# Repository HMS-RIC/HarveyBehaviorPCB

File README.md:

# HarveyBehaviorPCB v2
Circuit board for Harvey Lab VR behavior rigs

## Features
This board is designed to integrate a Teensy microcontroller and a National Instruments DAQ board (NI USB-600x) with the sensors and actuators on the behavior rig. Importantly, the board is used to convey the spherical treadmill movement signals to the VR computer. The Teensy makes a digital connection to the two ball movement sensors (mounted on the base of the spherical treadmill) to make continuous reading of ball movement. It then produces three analog outputs, representing velocity in the _Yaw_, _Pitch_, and _Roll_ axes, that are read into the VR computer by the DAQ board.

Other optional features of the PCB are: 
- Driver circuit for 2 solenoid valves (e.g. for liquid rewards)
- Two lick detector circuits
- A photodiode amplifier
- Many expansion ports/connectors: BNC connections, 0.1" headers, and a serial I2C connection (Qwiic connector)

## Fabrication
The full fabrication design is included in the [Gerber Zip File](PCB_v2_KiCAD/Gerbers/HarveyBehaviorPCB_v2.zip?raw=true). You can upload this file to any PCB fabricator to get a quote and place an order. (The board does not have any special features, so the default settings for PCB manufacture are probably fine.) One a relatively low-cost option for a board this size is the $33/board (3 board minimum) special at [Advanced Circuits](https://www.advancedpcb.com/en-us/33-each-special/).

## Assembly
The [Bill of Materials](HarveyBehaviorPCB_v2_BOM.xlsx?raw=true) (BOM) file has the full list of components. Everything but the optional I2C connector is a through-hole part and can be soldered on with a simple soldering iron (and [proper technique](https://mightyohm.com/files/soldercomic/FullSolderComic_EN.pdf)). The board is divided up into labeled regions that describe their high-level function and allow you to populate only the subset of components that you plan to use:
- **Ball sensor connectors**: The board is designed to work with two types of ball sensor ([ADNS-9800](https://www.tindie.com/products/citizenjoe/adns-9800-motion-sensor/) and [PMW3360](https://www.tindie.com/products/citizenjoe/pmw3360-motion-sensor/)). Chose one and populate the appropriate connector. (Also be sure to use the correct Teensy firmware for your ball sensor.)
- **Valve driver circuit**, **Lick and photodiode circuits**: These are optional functionalities. Only populate these regions if you plan to use them.
- **LP filters for velocity signals**: These are not optional. They low-pass filter the Teensy's digital (PWM) output to form a smooth analog signal for the NI board to acquire.
- **User 3/4 voltage-limiting circuit**: This is necessary if you plan to use the NI board's analog output pins (_AO-0_, _AO-1_) to control the voltage on _User-3_ and _User-4_. This circuit protects the Teensy from an accidental +5V output from the NI board (since the Teensy 4.0 cannot handle >3.3V inputs).
- **Jumpers JP2, JP3**: Optional. Short these jumpers (i.e., connect the pins within each jumper) to enable the NI analog output (_AO-0/1_, a.k.a. _User-3/4_) to control the valves.
- **Jumpers JP4, JP5**: Optional. In their default state they enable the I2C connector and disable the _MOT1_/_MOT2_ connections to the ball sensors. The _MOTx_ lines are not used during typical operation, so these jumpers are unlikely to be used.

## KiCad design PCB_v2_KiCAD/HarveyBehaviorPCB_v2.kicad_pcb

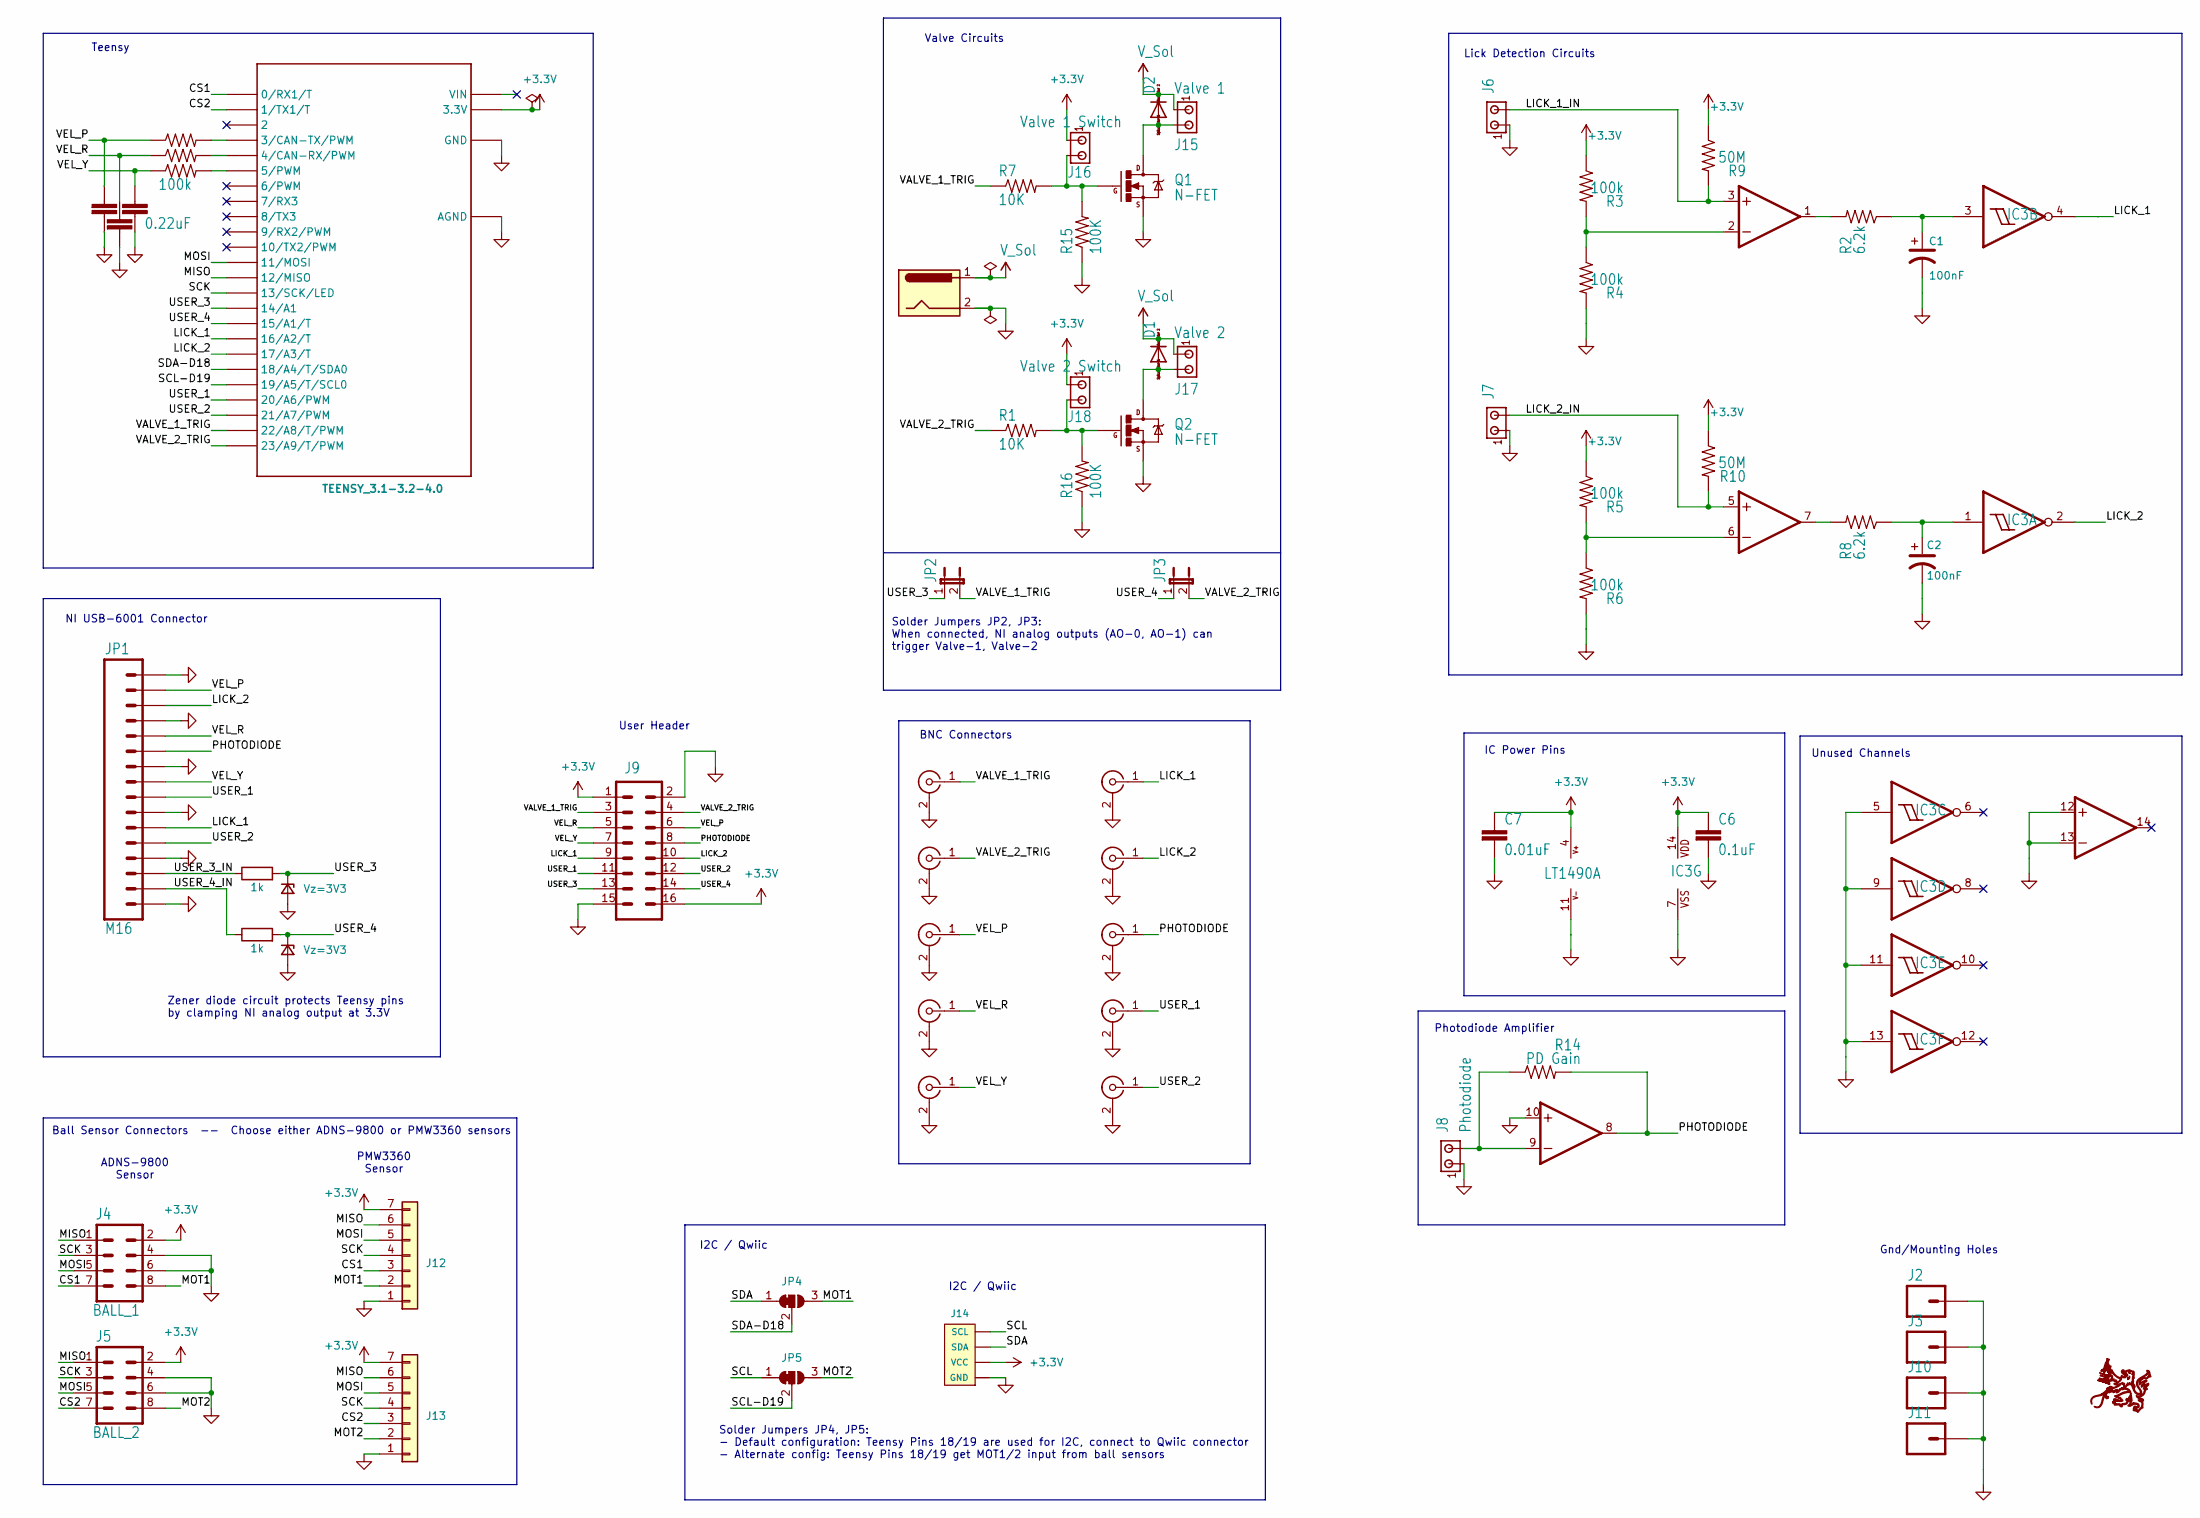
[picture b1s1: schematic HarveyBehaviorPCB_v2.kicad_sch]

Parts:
C1, C2: 100nF; CPOL-RADIAL-10UF-25V
C3, C4, C5: 0.22uF; CAP-PTH-SMALL2
C6: 0.1uF; CAP-PTH-SMALL-KIT
C7: 0.01uF; CAP-PTH-SMALL-KIT
D1, D2: 1N4148; DO41-10
D3, D4: Vz=3V3; D_DO-34_SOD68_P7.62mm_Horizontal
IC1: LT1490A; DIP-14_W7.62mm_LongPads
IC3: 40106N; DIP-14_W7.62mm_LongPads
J1: POWER_JACKPTH; POWER_JACK_PTH
J2, J3, J10, J11: M01SMTSO-256-ET-0.165DIA; SMTSO-256-ET-0.165DIA
J4: BALL_1; 2X4
J5: BALL_2; 2X4
J6, J7: MTA02-100; 10X02MTA
J8: Photodiode; 10X02MTA
J9: M08X2; 2X8
J12, J13: Conn_01x07; CON_535170730_MOL
J14: I2C_STANDARDQWIIC; 1X04_1MM_RA
J15: Valve 1; 10X02MTA
J16: Valve 1 Switch; 10X02MTA
J17: Valve 2; 10X02MTA
J18: Valve 2 Switch; 10X02MTA
JP1: M16; 1X16_TERM_BLOCK_0.15_
JP2, JP3: JUMPER-2PTH; 1X02
JP4, JP5: SolderJumper_3_Bridged12; SolderJumper-3_P1.3mm_Bridged12_RoundedPad1.0x1.5mm
Q1, Q2: N-FET; TO220V
R1, R7: 10K; AXIAL-0.5
R2, R8: 6.2k; AXIAL-0.5
R3, R4, R5, R6, R11, R12, R13: 100k; AXIAL-0.5
R9, R10: 50M; AXIAL-0.5
R14: PD Gain; AXIAL-0.5
R15, R16: 100K; AXIAL-0.5
R17, R18: 1k; R_Axial_DIN0207_L6.3mm_D2.5mm_P10.16mm_Horizontal
TEENSY0: TEENSY_3.1-3.2-4.0; TEENSY_3.0-3.2&LC_DIL
U$1, U$2, U$3, U$4, U$5, U$6, U$7, U$8, U$9, U$10: BNCPTH; BNC_Amphenol_B6252HB-NPP3G-50_Horizontal

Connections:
+3.3V: C6.1, C7.1, IC1.4 (V+), IC3.14 (VDD), J4.2, J5.2, J9.1, J9.16, J12.7, J13.7, J14.2 (VCC), J16.1, J18.1, R3.P$1 (1), R5.P$1 (1), R9.P$1 (1), R10.P$1 (1), TEENSY0.3.3V
/CS1: J4.7, J12.3, TEENSY0.0 (0/RX1/T)
/CS2: J5.7, J13.3, TEENSY0.1 (1/TX1/T)
/LICK_1: IC3.4 (O), J9.9, JP1.6, JP1.22 (6), TEENSY0.16/A2 (16/A2/T), U$6.1 (In)
/LICK_1_IN: IC1.3 (+IN), J6.2, R9.P$2 (2)
/LICK_2: IC3.2 (O), J9.10, JP1.14, JP1.30 (14), TEENSY0.17/A3 (17/A3/T), U$7.1 (In)
/LICK_2_IN: IC1.5 (+IN), J7.2, R10.P$2 (2)
/MISO: J4.1, J5.1, J12.6, J13.6, TEENSY0.12 (12/MISO)
/MOSI: J4.5, J5.5, J12.5, J13.5, TEENSY0.11 (11/MOSI)
/MOT1: J4.8, J12.2, JP4.3 (B)
/MOT2: J5.8, J13.2, JP5.3 (B)
/PHOTODIODE: IC1.8 (OUT), J9.8, JP1.11, JP1.27 (11), R14.P$2 (2), U$8.1 (In)
/SCK: J4.3, J5.3, J12.4, J13.4, TEENSY0.13 (13/SCK/LED)
/SCL: J14.4 (SCL), JP5.1 (A)
/SCL-D19: JP5.2 (C), TEENSY0.19/A5 (19/A5/T/SCL0)
/SDA: J14.3 (SDA), JP4.1 (A)
/SDA-D18: JP4.2 (C), TEENSY0.18/A4 (18/A4/T/SDA0)
/USER_1: J9.11, JP1.8, JP1.24 (8), TEENSY0.20/A6 (20/A6/PWM), U$9.1 (In)
/USER_2: J9.12, JP1.5, JP1.21 (5), TEENSY0.21/A7 (21/A7/PWM), U$10.1 (In)
/USER_3: D4.1 (K), J9.13, JP2.1, R18.2, TEENSY0.14/A0 (14/A1)
/USER_3_IN: JP1.3, JP1.19 (3), R18.1
/USER_4: D3.1 (K), J9.14, JP3.1, R17.2, TEENSY0.15/A1 (15/A1/T)
/USER_4_IN: JP1.2, JP1.18 (2), R17.1
/VALVE_1_TRIG: J9.3, JP2.2, R7.P$1 (1), TEENSY0.22/A8 (22/A8/T/PWM), U$1.1 (In)
/VALVE_2_TRIG: J9.4, JP3.2, R1.P$1 (1), TEENSY0.23/A9 (23/A9/T/PWM), U$2.1 (In)
/VEL_P: C5.1, J9.6, JP1.15, JP1.31 (15), R13.P$1 (1), U$3.1 (In)
/VEL_R: C4.1, J9.5, JP1.12, JP1.28 (12), R12.P$1 (1), U$4.1 (In)
/VEL_Y: C3.1, J9.7, JP1.9, JP1.25 (9), R11.P$1 (1), U$5.1 (In)
GND: C1.2 (-), C2.2, C3.2, C4.2, C5.2, C6.2, C7.2, D3.2 (A), D4.2 (A), IC1.10 (+IN), IC1.11 (V-), IC1.12 (+IN), IC1.13 (-IN), IC3.5 (I), IC3.7 (VSS), IC3.9 (I), IC3.11 (I), IC3.13 (I), J1.2, J2.P$1 (1), J3.P$1 (1), J4.4, J4.6, J5.4, J5.6, J6.1, J7.1, J8.1, J9.2, J9.15, J10.P$1 (1), J11.P$1 (1), J12.1, J13.1, J14.1 (GND), JP1.1, JP1.4, JP1.7, JP1.10, JP1.13, JP1.16, JP1.17 (1), JP1.20 (4), JP1.23 (7), JP1.26 (10), JP1.29 (13), JP1.32 (16), Q1.3 (S), Q2.3 (S), R4.P$2 (2), R6.P$2 (2), R15.P$1 (1), R16.P$1 (1), TEENSY0.AGND, TEENSY0.GND, U$1.2 (Ext), U$2.2 (Ext), U$3.2 (Ext), U$4.2 (Ext), U$5.2 (Ext), U$6.2 (Ext), U$7.2 (Ext), U$8.2 (Ext), U$9.2 (Ext), U$10.2 (Ext)
unnamed: C1.1 (+), IC3.3 (I), R2.P$1 (1)
unnamed: IC1.2 (-IN), R3.P$2 (2), R4.P$1 (1)
unnamed: IC1.1 (OUT), R2.P$2 (2)
unnamed: IC1.6 (-IN), R5.P$2 (2), R6.P$1 (1)
unnamed: IC1.7 (OUT), R8.P$2 (2)
unnamed: IC1.9 (-IN), J8.2, R14.P$1 (1)
unnamed: C2.1, IC3.1 (I), R8.P$1 (1)
unnamed: D2.A, J15.2, Q1.2 (D)
unnamed: J16.2, Q1.1 (G), R7.P$2 (2), R15.P$2 (2)
unnamed: D1.A, J17.2, Q2.2 (D)
unnamed: J18.2, Q2.1 (G), R1.P$2 (2), R16.P$2 (2)
unnamed: R11.P$2 (2), TEENSY0.5 (5/PWM)
unnamed: R12.P$2 (2), TEENSY0.4 (4/CAN-RX/PWM)
unnamed: R13.P$2 (2), TEENSY0.3 (3/CAN-TX/PWM)
V_Sol: D1.C, D2.C, J1.1, J15.1, J17.1

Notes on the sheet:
NI USB-6001 Connector
Zener diode circuit protects Teensy pins by clamping NI analog output at 3.3V
BNC Connectors
Lick Detection Circuits
I2C / Qwiic
Photodiode Amplifier
Valve Circuits
Gnd/Mounting Holes
User Header
ADNS-9800 Sensor
Solder Jumpers JP4, JP5: - Default configuration: Teensy Pins 18/19 are used for I2C, connect to Qwiic connector - Alternate config: Teensy Pins 18/19 get MOT1/2 input from ball sensors
IC Power Pins
Teensy
Solder Jumpers JP2, JP3: When connected, NI analog outputs (AO-0, AO-1) can trigger Valve-1, Valve-2
Unused Channels
PMW3360 Sensor
Ball Sensor Connectors -- Choose either ADNS-9800 or PMW3360 sensors

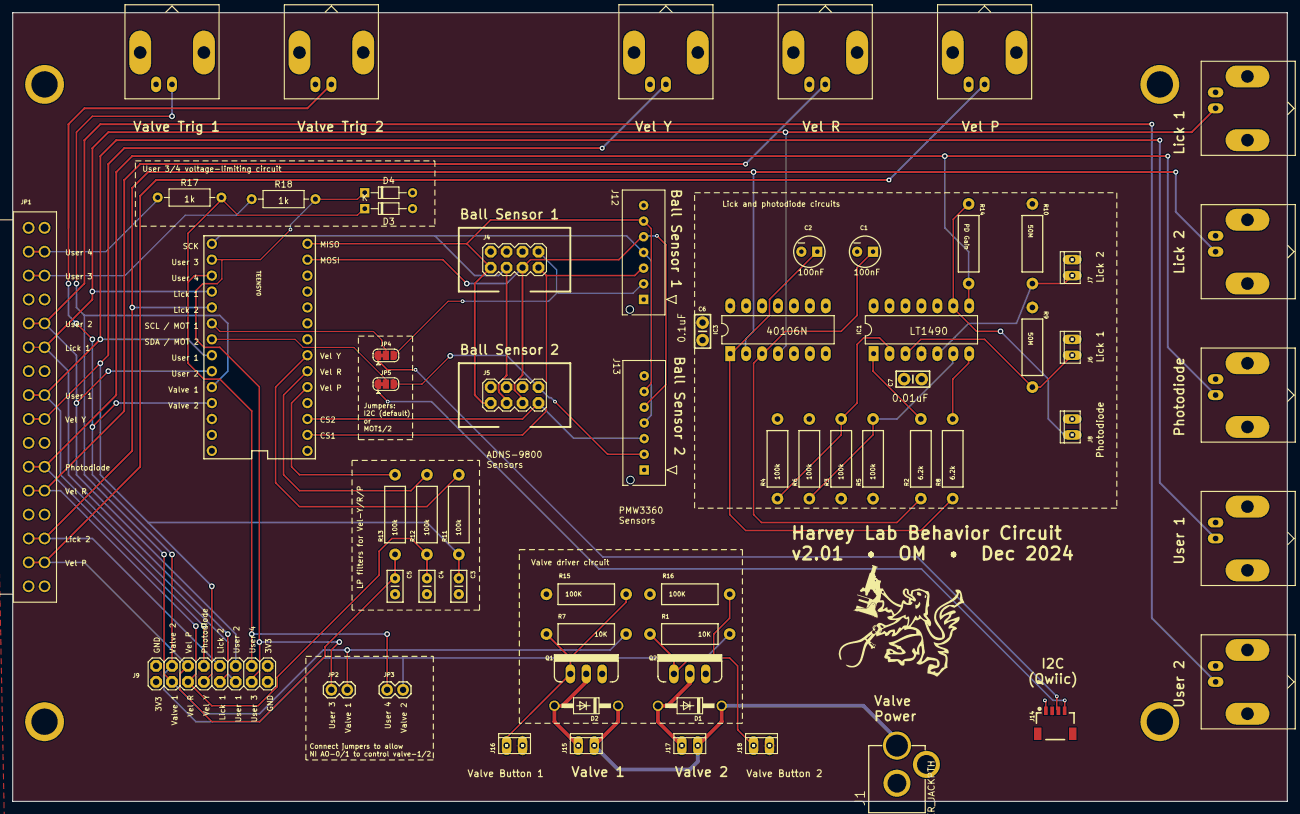
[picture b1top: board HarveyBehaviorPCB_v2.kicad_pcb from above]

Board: 2 copper layers, 203.2 x 125.7 mm, 67 parts (0 on the bottom side), 44 nets.

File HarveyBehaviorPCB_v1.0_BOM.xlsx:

Part | Value | Device | Package | Description
C1 | 100nF
C2 | 100nF
C3 | 0.22uF
C4 | 0.22uF
C5 | 0.22uF
C6 | 0.1uF
C7 | 0.01uF
D1 | 1N4148 | 1N4004 |  | DIODE
D2 | 1N4148 | 1N4004 |  | DIODE
IC1 | LT1490A |  |  | Quad Wideband, Low Power Current Feedback OP AMP
IC3 | 40106N |  |  | Hex SCHMITT TRIGGER
J1 |  |  |  | Power Jack
J2 |  | M01SMTSO-256-ET-0.165DIA | SMTSO-256-ET-0.165DIA | Header 1
J3 |  | M01SMTSO-256-ET-0.165DIA | SMTSO-256-ET-0.165DIA | Header 1
J4 | BALL_1 | M04X2 | 2X4 | .1 header | two rows of four."
J5 | BALL_2 | M04X2 | 2X4 | .1 header | two rows of four."
J6 |  | MTA02-100 | 10X02MTA | AMP connector
J7 |  | MTA02-100 | 10X02MTA | AMP connector
J8 | Photodiode | MTA02-100 | 10X02MTA | AMP connector
J9 |  | M08X2 | 2X8 | .1 headers | two rows of 8 each"
J10 |  | M01SMTSO-256-ET-0.165DIA | SMTSO-256-ET-0.165DIA | Header 1
J11 |  | M01SMTSO-256-ET-0.165DIA | SMTSO-256-ET-0.165DIA | Header 1
J15 | Valve 1 | MTA02-100 | 10X02MTA | AMP connector
J16 | Valve 1 Switch | MTA02-100 | 10X02MTA | AMP connector
J17 | Valve 2 | MTA02-100 | 10X02MTA | AMP connector
J18 | Valve 2 Switch | MTA02-100 | 10X02MTA | AMP connector
JP1 | M16 | M16 | 1X16_TERM_BLOCK_0.15",1x16 .1" header"
Q1 | MOSFET-NCHANNELFQP30N06L |  | TO220V | Common NMOSFET Parts
Q2 | MOSFET-NCHANNELFQP30N06L |  | TO220V | Common NMOSFET Parts
R1 | 10K |  |  | Resistor
R2 | 6.2k |  |  | Resistor
R3 | 100k |  |  | Resistor
R4 | 100k |  |  | Resistor
R5 | 100k |  |  | Resistor
R6 | 100k |  |  | Resistor
R7 | 10K |  |  | Resistor
R8 | 6.2k |  |  | Resistor
R9 | 50M |  |  | Resistor
R10 | 50M |  |  | Resistor
R11 | 100k |  |  | Resistor
R12 | 100k |  |  | Resistor
R13 | 100k |  |  | Resistor
R14 | PD Gain |  |  | Resistor
TEENSY | TEENSY_3.1-3.2_DIL | TEENSY_3.1-3.2_DIL | TEENSY_3.0-3.2&LC_DIL | Teensy 3.1 or 3.2 in a DIL Layout.
U$1 | BNCPTH | BNCPTH | BNC | BNC Connector, Mouser Part# 5227161
U$2 | BNCPTH | BNCPTH | BNC | BNC Connector, Mouser Part# 5227161
U$3 | BNCPTH | BNCPTH | BNC | BNC Connector, Mouser Part# 5227161
U$4 | BNCPTH | BNCPTH | BNC | BNC Connector, Mouser Part# 5227161
U$5 | BNCPTH | BNCPTH | BNC | BNC Connector, Mouser Part# 5227161
U$6 | BNCPTH | BNCPTH | BNC | BNC Connector, Mouser Part# 5227161
U$7 | BNCPTH | BNCPTH | BNC | BNC Connector, Mouser Part# 5227161
U$8 | BNCPTH | BNCPTH | BNC | BNC Connector, Mouser Part# 5227161
U$9 | BNCPTH | BNCPTH | BNC | BNC Connector, Mouser Part# 5227161
U$10 | BNCPTH | BNCPTH | BNC | BNC Connector, Mouser Part# 5227161

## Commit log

2018-10-03 initial commit (v1.2)
2018-10-03 Rename some files
2018-10-03 Create LICENSE
2018-10-03 Add PDF of schematic for v1.2
2024-10-01 Convert to KiCad and update design to v2.0
2024-10-07 Make Gerbers for v2.0
2024-11-08 Update .gitignore; Add datasheet for ball sensor cable
2024-11-08 Remove backup files
2024-11-08 Rearrange files
2024-11-27 Update PCB render
2024-12-02 [PCB] Increase width of copper pads on a few footprints; v2.0 -> v2.01
2024-12-05 Update BOM
2024-12-05 Update HarveyBehaviorPCB_v2_BOM.xlsx
    Added the Digikey part # for the capacitors
2025-01-03 Fix spelling errors
